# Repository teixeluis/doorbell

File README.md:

# Kinetic Doorbell Wifi Expansion

## Overview

This project appeared from the need for connecting a kinetic doorbell to my home automation.

This doorbell solution appealed me for not requiring power on the transmitter side 
(the doorbell button sitting outside), as it relies on the kinetic energy of the user 
pressing the button. The experience is of clicking a button with slightly more travel amplitude 
than usual, but comparable to pressing a traditional wired doorbell button (e.g. Legrand push 
button).

Like I had previously done with another doorbell (this time a battery powered one - CR2032 
coin cell), the first thing I tried was leveraging a modified Sonoff RF Bridge (flashed with
Tasmota on the ESP8266 and Portisch firmware on the radio decoder chip), in order to capture 
the transmitted frames and feed MQTT events into my home automation.

However I learned that the frames sent by the kinetic transmitter are too short (power budget
constraints are a very likely factor here) for the RF baseband and/or decoder chip to detect,
therefore preventing my existing setup from be used here.

Then, given my interest in getting these events, I decided to pursuit another route: instead
of trying to capture the radio signal independently, I have chosen to focus on the doorbell
receiver and see if I could come up with a hardware solution.

## Solution

### Partial reverse-engineering

As I was investigating the doorbell receiver, I could tell that the functions in this board 
were well divided in 3 different 8-pin chips: one being the RF receiver, clealy identifiable by the
27.1412 MHz crystal next to it. While the labels in the package don't have any obvious part
correspondence (it has only the indications 004 2342d00252), there is a strong probability
of being the CMT2210LH 433 MHz OOK/ASK receiver:

Then there is what apparently is the microcontroller where probably the raw (digital) signal 
discriminated by the radio chip, is decoded into recognizable frames, and (as I latter learned) 
where the bitstream containing the sequence of sounds to be played is stored and played. 
By tapping into the output pins, I could see this flow of bits being output while the 
sound / melody was being played.

Lastly the audio chip, which appears to be a combination of FM (or similar synthesis function)
and analog audio production and amplification. Two of the pins of this last 8-pin chip, are
connected directly to the small built-in speaker.

Conveniently, in the back of the receiver PCB there were test pads allowing access to all of these
relevant signals, and also the speaker pins.

### My expansion board

With these findings I had more than enough material for my goal. Having a signal that changes
when the melody starts playing, would be a solid indication that someone had pressed the 
doorbell button. Also, I could go a bit further by taking into consideration that I could 
also tap into the song selection and volume buttons, allowing me to also control these 
via software.

As such, I went on to build a board allowing me to:

 * power the doorbell original PCB and the expansion board itself. The doorbell originally
operated at 5 Volts but by testing, I could tell that it was equally happy running at 3.3 Volts.
For my design this was a major difference, because it meant a substantial saving in components
and complexity;
 * allow events from the doorbell to be mediated into the home automation via an ESP32
microcontroller;
 * control the playback, volume and song selection through the ESP32;
 * nice to have - inject my own sequences, creating new melodies / sounds (TBD);
 * have a more powerful speaker and audio output through the addition of an external audio OPAMP.

With this in mind, so I went. Keeping the design simple while allowing for providing the functions
described above.

#### Project

The board consists of an ESP32-WROOM-32 module, a 3.3 Volt linear regulator (to drop the +12V supply
to the 3.3V required by the ESP32 and the doorbell PCB), and a 6 Watt audio amplifier. For the 
regulator I have chosen the common AMS1117 low dropout chip, whereas for the audio opamp, I have
selected the TDA1517P chip. The reason for choosing the latter was because I had a few of these in
stock, and is a basic yet decent amplifier. It is a stereo chip, but in this project I am only using
one of the two channels.

Because I didn't want to limit the board's purpose in the future, I decided to leave all the relevant 
taps (volume control, song control, and audio bitstream), all tied to GPIO ports in the ESP32 chip. 
For the audio bitstream, I have assigned two GPIO's in order to achieve bidirectional interaction with 
the chip.

For the audio, because I found the output that goes to the original speaker, to be a PWM signal 
modulated with a 128 KHz carrier (basically we are dealing with a class D audio amplifier), I could not
feed it directly to the linear audio OPAMP. The carrier signal had to be filtered first. As such
I have chosen to use a 1:1 audio transformer, together with an RC network on the transformer
secoondary in order to provide a clean signal to the OPAMP input.

In order to control the volume level (depending on where this module is placed, max volume can easily become too unpleasant), I have added a 100 K potentiometer.

This board requires a 12 Volts supply because of the audio amplifier. It can be jacked up to
15 Volts, but more than that should be avoided because of the AMS1117 input voltage limits.
More voltage will of course mean potentially higher amplitude in the speaker, therefore
implying more intense audio.

#### Assembled hardware

I left space in the board design for mounting the small doorbell PCB as daughter board,
in order to slighly simplify the mechanical design, and to keep the connections between the
two boards in close proximity.

There is a 7 pin header for programming and/or debugging (serial log) the ESP32 chip.
The initial programming entirely depends on it because of the absence of any pre-programmed
code to update the firmware via Wifi.

## Sample code

In the `doorbell.be` file you may find a small script that all it does is to engage the 
song selection and volume keys, and also has experimental logic to inject a stream of
pulses into the audio chip, in an attempt to understand its protocol.

## Future steps

While it poses some challenges, one interesting idea for this project is to tackle the
audio bitstream, and be able to produce custom songs via the ESP32 chip. However the 
effort / reward relationship needs to be put into the equation, considering the numerous
(and well known) hardware solutions available for the same result.

In my perspective it is more interesting for the fun of reverse engineering that feature,
than the concrete added value of achieving it.

## Included materials

In this project you can find the Tasmota / Berry source code for the test script I mentioned, 
as well as in the hardware/cad/doorbell section, the schematic and CAD drawings. There are
also a few footprint customizations.

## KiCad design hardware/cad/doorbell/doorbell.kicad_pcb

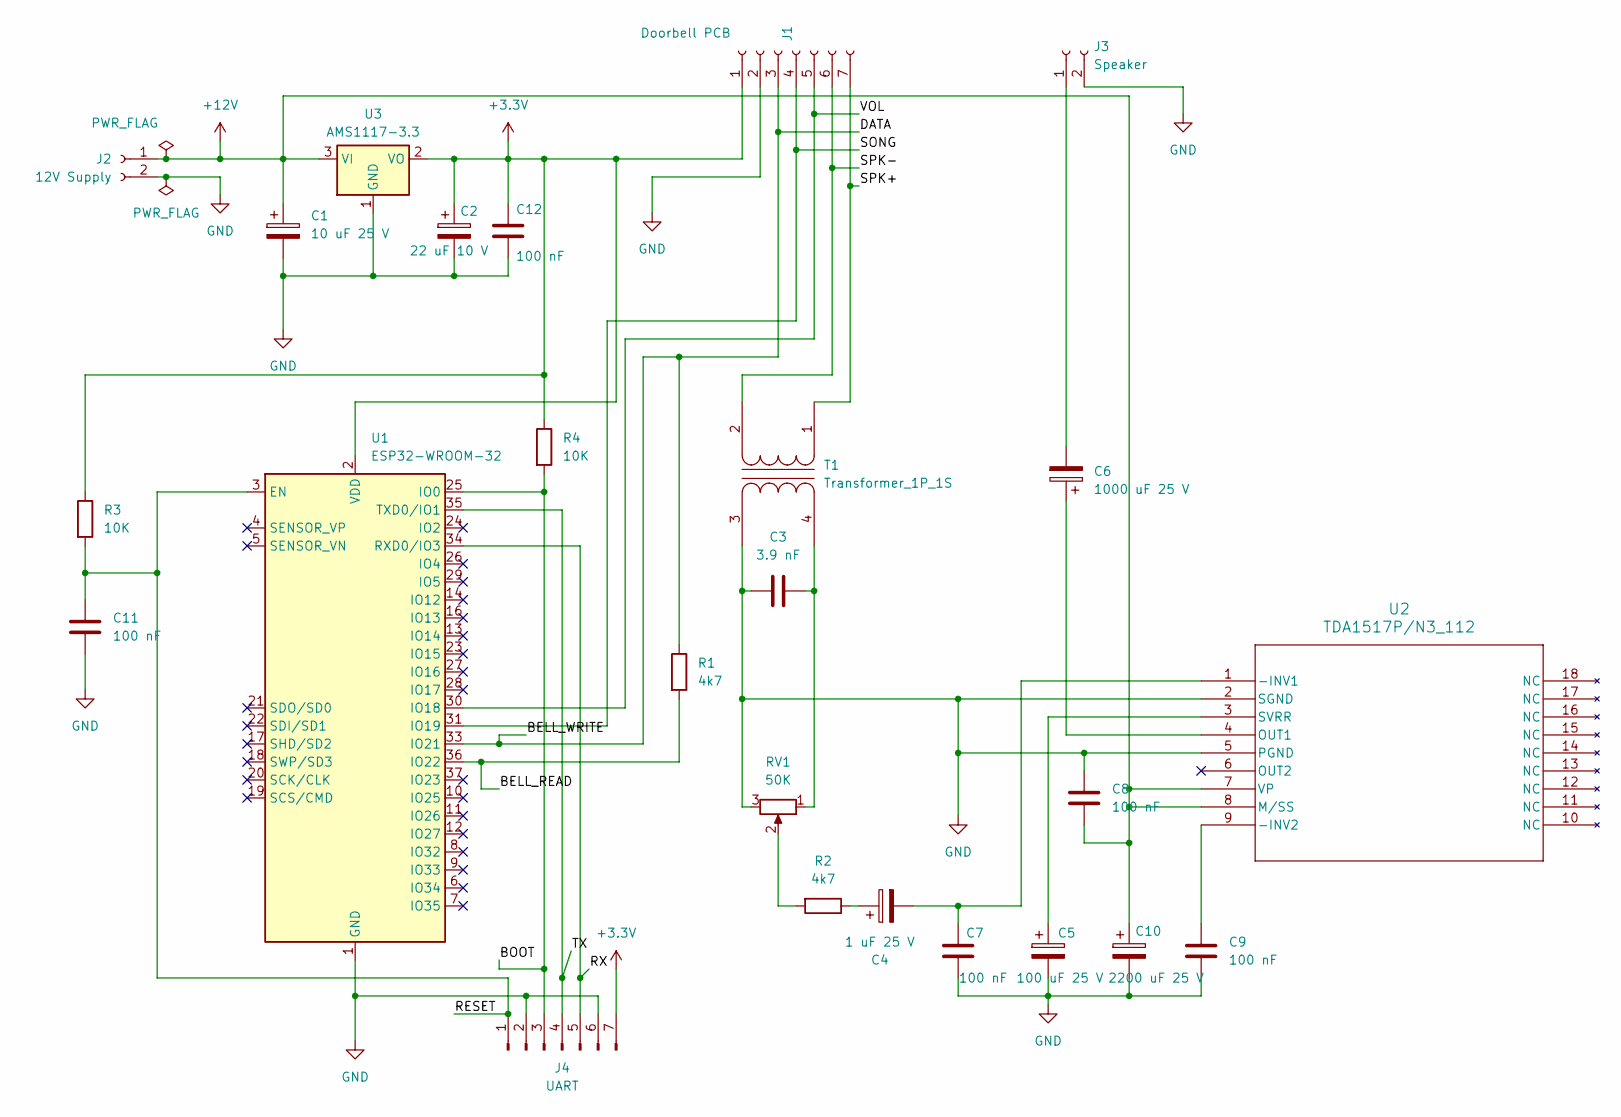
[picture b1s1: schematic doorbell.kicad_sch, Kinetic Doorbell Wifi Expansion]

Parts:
C1: 10 uF 25 V; CP_Radial_D4.0mm_P1.50mm
C2: 22 uF 10 V; CP_Radial_D5.0mm_P2.00mm
C3: 3.9 nF; C_Disc_D6.0mm_W2.5mm_P5.00mm
C4: 1 uF 25 V; CP_Radial_D5.0mm_P2.00mm
C5: 100 uF 25 V; CP_Radial_D5.0mm_P2.00mm
C6: 1000 uF 25 V; CP_Radial_D10.0mm_P3.80mm
C7, C8, C9, C11, C12: 100 nF; C_Disc_D10.0mm_W2.5mm_P5.00mm
C10: 2200 uF 25 V; CP_Radial_D12.5mm_P5.00mm
J1: Doorbell PCB; JST_PH_B7B-PH-K_1x07_P2.00mm_Vertical
J2: 12V Supply; JST_PH_B2B-PH-K_1x02_P2.00mm_Vertical
J3: Speaker; JST_PH_B2B-PH-K_1x02_P2.00mm_Vertical
J4: UART; PinHeader_1x07_P2.54mm_Vertical
R1, R2: 4k7; R_Axial_DIN0207_L6.3mm_D2.5mm_P10.16mm_Horizontal
R3, R4: 10K; R_Axial_DIN0207_L6.3mm_D2.5mm_P10.16mm_Horizontal
RV1: 50K; Potentiometer_Piher_PT-15-H05_Horizontal
T1: Transformer_1P_1S; Transformer_NF_ETAL_P1165
U1: ESP32-WROOM-32
U2: TDA1517P/N3_112; DIP-18_W7.62mm
U3: AMS1117-3.3; SOT-223-3_TabPin2

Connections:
+3.3V: C2.1, C12.1, J1.1, J4.7, R3.1, R4.1, U1.2 (VDD), U3.2 (VO)
+12V: C1.1, C8.2, C10.1, J2.1, U2.7 (VP), U2.8 (M/SS), U3.3 (VI)
/BELL_READ: R1.2, U1.36 (IO22)
/BELL_WRITE: J1.3, R1.1, U1.33 (IO21)
/BOOT: J4.3, R4.2, U1.25 (IO0)
/RESET: C11.1, J4.1, R3.2, U1.3 (EN)
/RX: J4.5, U1.34 (RXD0/IO3)
/SONG: J1.4, U1.31 (IO19)
/SPK+: J1.7, T1.1 (AA)
/SPK-: J1.6, T1.2 (AB)
/TX: J4.4, U1.35 (TXD0/IO1)
/VOL: J1.5, U1.30 (IO18)
GND: C1.2, C2.2, C3.2, C5.2, C7.2, C8.1, C9.2, C10.2, C11.2, C12.2, J1.2, J2.2, J3.2, J4.2, J4.6, RV1.3, T1.3 (SA), U1.1 (GND), U1.15 (GND), U1.38 (GND), U1.39 (GND), U2.2 (SGND), U2.5 (PGND), U3.1 (GND)
unnamed: C4.1, R2.1
unnamed: C6.2, J3.1
unnamed: R2.2, RV1.2
unnamed: C3.1, RV1.1, T1.4 (SB)
unnamed: C4.2, C7.1, U2.1 (-INV1)
unnamed: C9.1, U2.9 (-INV2)
unnamed: C6.1, U2.4 (OUT1)
unnamed: C5.1, U2.3 (SVRR)

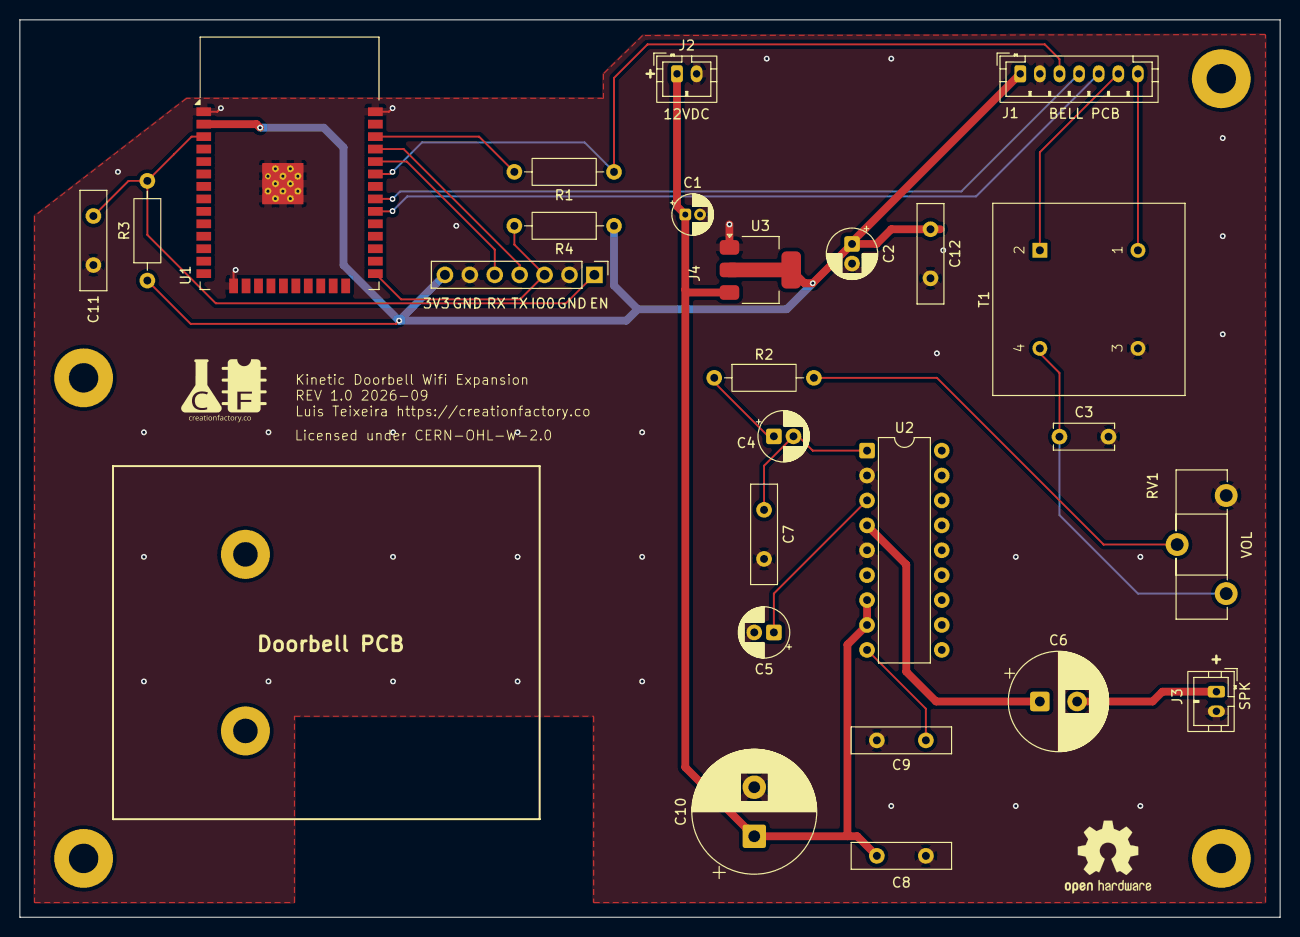
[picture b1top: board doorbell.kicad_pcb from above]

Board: 2 copper layers, 128.5 x 91.5 mm, 31 parts (0 on the bottom side), 21 nets.

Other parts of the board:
DB_PCB_01: MountingHole_2.5mm_Pad
DB_PCB_02: MountingHole_2.5mm_Pad
LB_HOLE: MountingHole_3mm_Pad
LT_HOLE: MountingHole_3mm_Pad
RB_HOLE: MountingHole_3mm_Pad
RT_HOLE: MountingHole_3mm_Pad

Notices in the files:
hardware/cad/doorbell/doorbell.kicad_pcb:
Licensed under CERN-OHL-W-2.0
